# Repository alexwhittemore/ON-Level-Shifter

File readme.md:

The ON Level Shifter is a two channel, unidirectional level shifter targeted at UART serial connections. It is implemented using two ON Semi MC74VHC1GT126 devices. These buffer a TTL input (Vil <.8V, Vih >2V) to a CMOS output (Voh > .8VCC, Vol < .1VCC). They are tolerant of up to 7V input regardless of VCC, and function with VCC as low as 3V, making them ideal for interfacing 2.5 or 3.3V logic on the low side with 3.3 or 5V logic on the high side.

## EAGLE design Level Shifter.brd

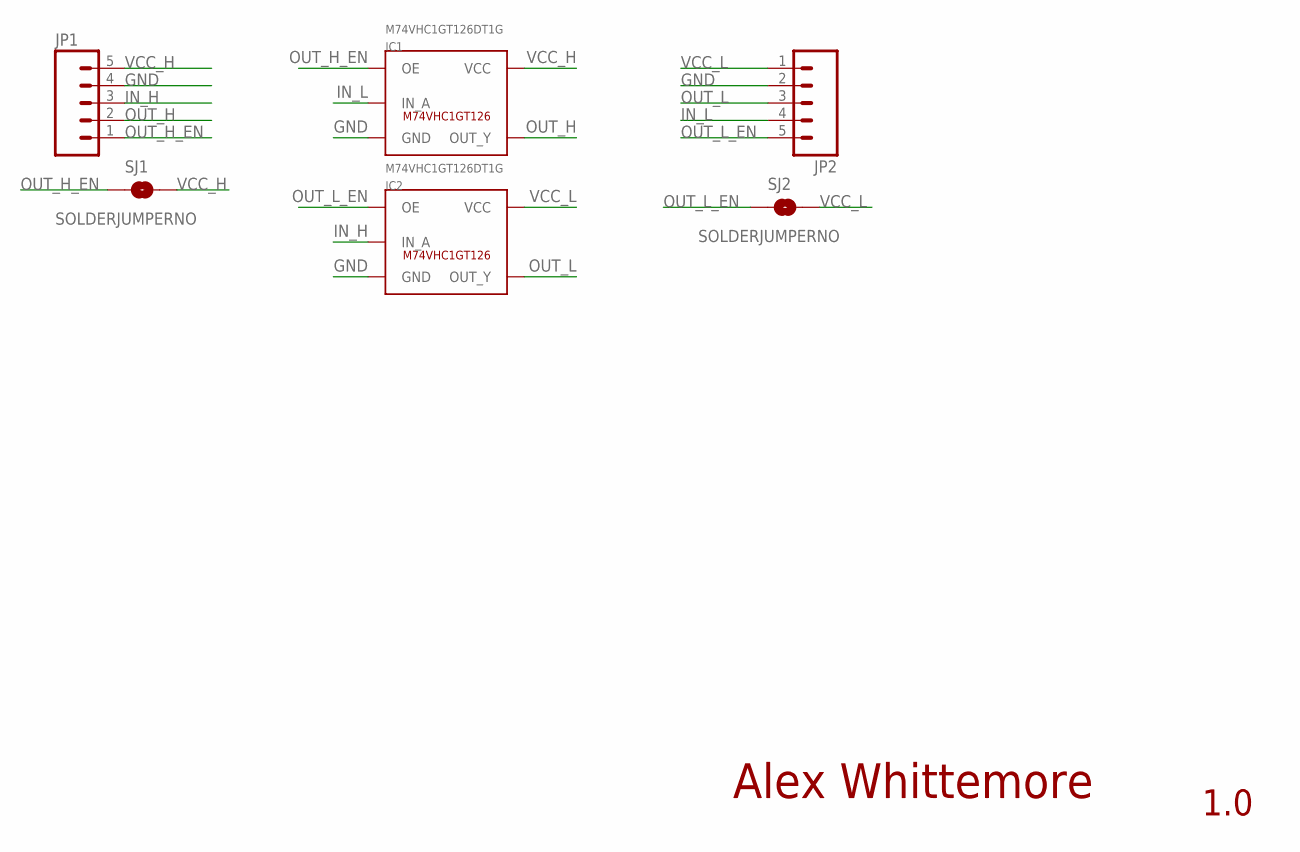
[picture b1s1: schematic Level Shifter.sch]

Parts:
IC1, IC2: M74VHC1GT126DT1G; SOT23-5L
JP1, JP2: M05LOCK; 1X05_LOCK
SJ1, SJ2: SOLDERJUMPERNO; SJ_2S-NO

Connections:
GND: IC1.3 (GND), IC2.3 (GND), JP1.4, JP2.2
IN_H: IC2.2 (IN_A), JP1.3
IN_L: IC1.2 (IN_A), JP2.4
OUT_H: IC1.4 (OUT_Y), JP1.2
OUT_H_EN: IC1.1 (OE), JP1.1, SJ1.1
OUT_L: IC2.4 (OUT_Y), JP2.3
OUT_L_EN: IC2.1 (OE), JP2.5, SJ2.1
VCC_H: IC1.5 (VCC), JP1.5, SJ1.2
VCC_L: IC2.5 (VCC), JP2.1, SJ2.2

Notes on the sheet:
Alex Whittemore
1.0

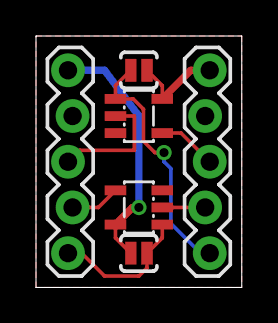
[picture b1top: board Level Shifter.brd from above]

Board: 2 copper layers, 11.4 x 14.0 mm, 6 parts (0 on the bottom side), 9 nets.

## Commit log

2012-09-17 Initial commit of the level shifter board.
2012-09-17 Added a readme.md describing the project
2013-06-20 ignore eagle.epf

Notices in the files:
parts and their libraries:
SparkFun-Connectors: Licensing: CC v3.0 Share-Alike You are welcome to use this library for commercial purposes.
AlexW-Eagle-Libraries: Released under the Creative Commons
AlexW-Eagle-Libraries: http://creativecommons.org/licenses/by-sa/3.0
